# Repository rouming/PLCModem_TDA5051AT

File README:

This is DC low voltage (up to 60v) LC PLC modem based on TDA5051AT chip.
Firmware is written for STM32F103 BluePill board.  Modem PCB is designed
in such a way that BluePill can be directly pluged in using hardware
USART1 support.

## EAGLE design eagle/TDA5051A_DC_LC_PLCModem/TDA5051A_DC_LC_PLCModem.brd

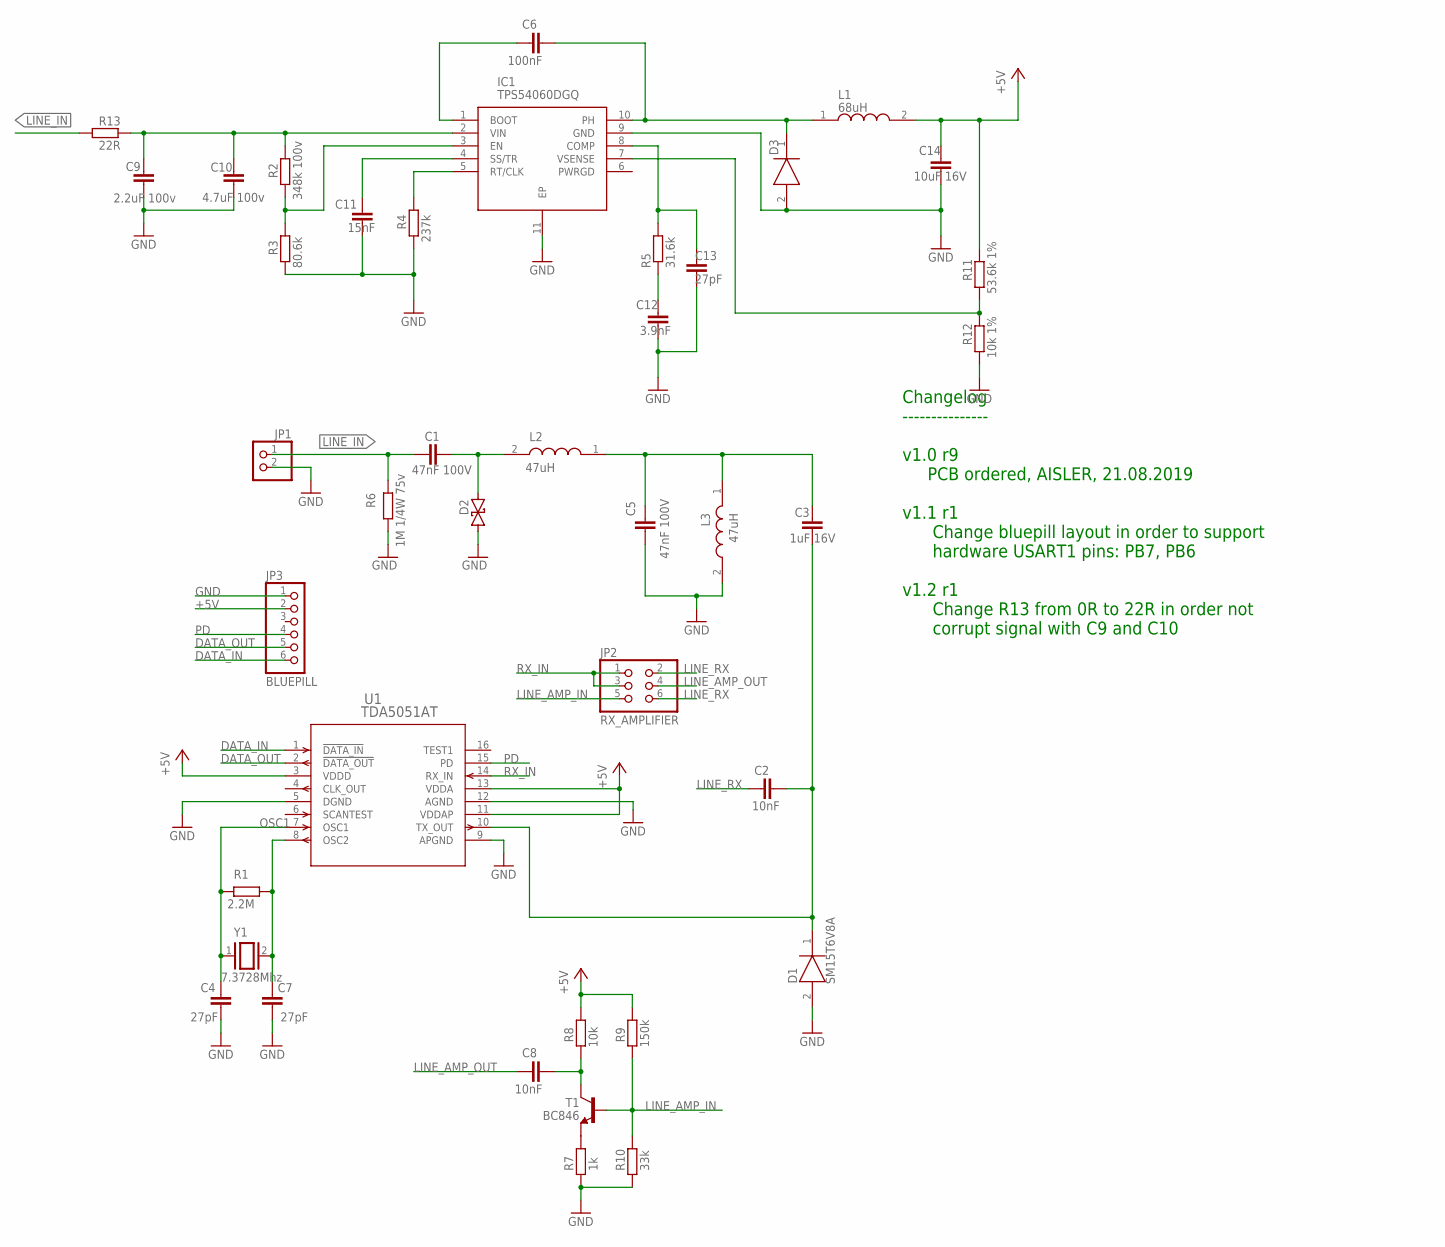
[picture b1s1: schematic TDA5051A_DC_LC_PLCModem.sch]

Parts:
C1, C5: 47nF 100V; C1206; MPN C1206C473K1RACAUTO
C2, C8: 10nF; C0603; MPN C0603C103K5RACAUTO7411
C3: 1uF 16V; C0805; MPN C0805C105K4RACAUTO
C4, C7, C13: 27pF; C0603; MPN 06035A270JAT2A
C6: 100nF; C0603; MPN C0603C104K5RECAUTO
C9: 2.2uF 100v; C1210; MPN C3225X7R2A225K230AB
C10: 4.7uF 100v; C1210; MPN CGA6M3X7S2A475K200AB
C11: 15nF; C0603; MPN 06035C153KAT2A
C12: 3.9nF; C0603; MPN GCM1885C1H392JA16D
C14: 10uF 16V; C0603; MPN GRM188R61C106KAALD
D1: SM15T6V8A; DIOM8059X265N; MPN SM15T6V8A
D2: SM15T6V8CA; DIOM8059X265N; MPN SM15T6V8CA
D3: STPS2H100A; DIOM5126X265N; MPN STPS2H100A
IC1: TPS54060DGQ; SOP50P490X110-11N; MPN TPS54060DGQR
JP1: PINHD-1X2; 1X02
JP2: RX_AMPLIFIER; 2X03
JP3: BLUEPILL; 1X06; MPN M20-7820646
L1: 68uH; SDR0805-680KL; MPN SDR0805-680KL
L2, L3: 47uH; SDR1307-220ML; MANUFACTURER_PART_NUMBER SDR1307A-470K; MOUSER_PART_NUMBER 652-SDR1307A-470K
R1: 2.2M; R0603; MPN RC0603JR-072M2L
R2: 348k 100v; R0603; MPN RG1608P-3483-D-T5
R3: 80.6k; R0603; MPN CRCW060380K6FKEA
R4: 237k; R0603; MPN AC0603FR-07237KL
R5: 31.6k; R0603; MPN AC0603FR-0731K6L
R6: 1M 1/4W 75v; R0603; MPN RCS06031M00FKEA
R7: 1k; R0603; MPN CRCW06031K00FKEAC
R8: 10k; R0603; MPN CRCW060310K0FKEAC
R9: 150k; R0603; MPN RC0603FR-07150KL
R10: 33k; R0603; MPN RC0603FR-0733KL
R11: 53.6k 1%; R0603; MPN RC0603FR-0753K6L
R12: 10k 1%; R0603; MPN CRCW060310K0FKEAC
R13: 22R; R0603; MPN RC0603JR-070RL
T1: BC846; SOT23; MPN BC846BLT1G
U1: TDA5051AT; SOT162-1; MPN TDA5051AT/C1,518
Y1: 7.3728Mhz; HC/49US_(AT49); MPN ABLS-7.3728MHZ-B2-T

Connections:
+5V: C14.1, JP3.2, L1.2, R8.2, R9.2, R11.2, U1.3 (VDDD), U1.11 (VDDAP), U1.13 (VDDA)
DATA_IN: JP3.6, U1.1 (!DATA_IN)
DATA_OUT: JP3.5, U1.2 (!DATA_OUT)
GND: C4.1, C5.1, C7.1, C9.2, C10.2, C11.2, C12.2, C13.2, C14.2, D1.2 (A), D2.2, D3.2 (A), IC1.9 (GND), IC1.11 (EP), JP1.2, JP3.1, L3.2, R3.1, R4.1, R6.2, R7.1, R10.1, R12.1, U1.5 (DGND), U1.9 (APGND), U1.12 (AGND)
LINE_AMP_IN: JP2.5, R9.1, R10.2, T1.1 (B)
LINE_AMP_OUT: C8.1, JP2.4
LINE_IN: C1.1, JP1.1, R6.1, R13.1
LINE_IN1: C9.1, C10.1, IC1.2 (VIN), R2.2, R13.2
LINE_RX: C2.1, JP2.2, JP2.6
unnamed: C2.2, C3.2, D1.1 (K), U1.10 (TX_OUT)
unnamed: C1.2, D2.1, L2.2
unnamed: C3.1, C5.2, L2.1, L3.1
unnamed: C8.2, R8.1, T1.3 (C)
unnamed: C6.1, IC1.1 (BOOT)
unnamed: C6.2, D3.1 (K), IC1.10 (PH), L1.1
unnamed: R7.2, T1.2 (E)
unnamed: C7.2, R1.2, U1.8 (OSC2), Y1.2
unnamed: IC1.3 (EN), R2.1, R3.2
unnamed: IC1.5 (RT/CLK), R4.2
unnamed: C11.1, IC1.4 (SS/TR)
unnamed: C12.1, R5.1
unnamed: C13.1, IC1.8 (COMP), R5.2
unnamed: IC1.7 (VSENSE), R11.1, R12.2
OSC1: C4.2, R1.1, U1.7 (OSC1), Y1.1
PD: JP3.4, U1.15 (PD)
RX_IN: JP2.1, JP2.3, U1.14 (RX_IN)
TEST1: U1.16 (TEST1)

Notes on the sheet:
Changelog --------------- v1.0 r9 PCB ordered, AISLER, 21.08.2019 v1.1 r1 Change bluepill layout in order to support hardware USART1 pins: PB7, PB6 v1.2 r1 Change R13 from 0R to 22R in order not corrupt signal with C9 and C10

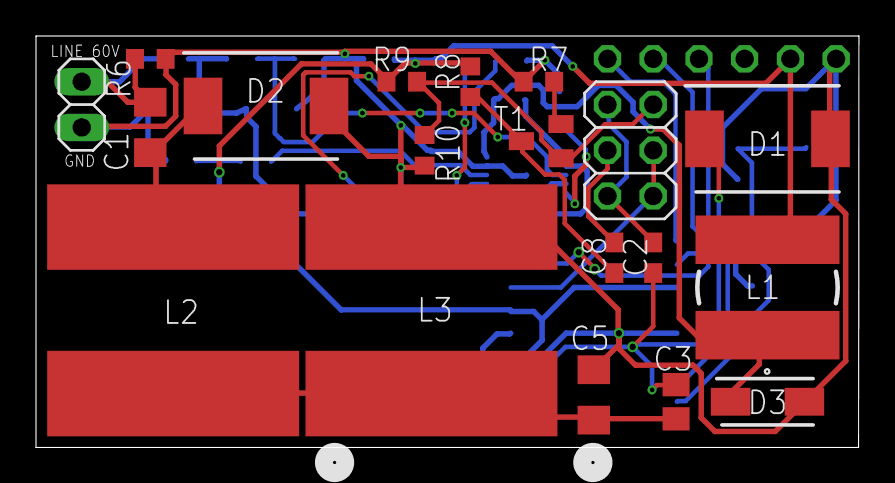
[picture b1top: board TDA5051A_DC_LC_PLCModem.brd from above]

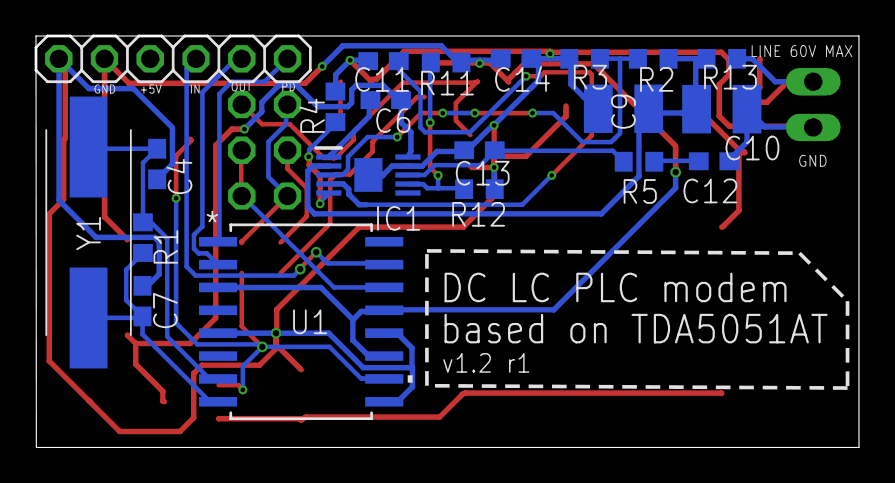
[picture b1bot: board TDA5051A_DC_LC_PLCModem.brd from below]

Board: 2 copper layers, 45.7 x 22.9 mm, 40 parts (21 on the bottom side), 26 nets.

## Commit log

2019-09-01 Initial.
2019-09-19 Add .gitignore
2019-09-24 Add README
2019-09-24 Add datasheets
2019-09-24 Add EAGLE schematics and board
2019-09-24 Implement USART send
2019-10-06 firmware: fix sequence check
    Reinit local sequence value if slave does not receive a valid
    sequence from a master.
